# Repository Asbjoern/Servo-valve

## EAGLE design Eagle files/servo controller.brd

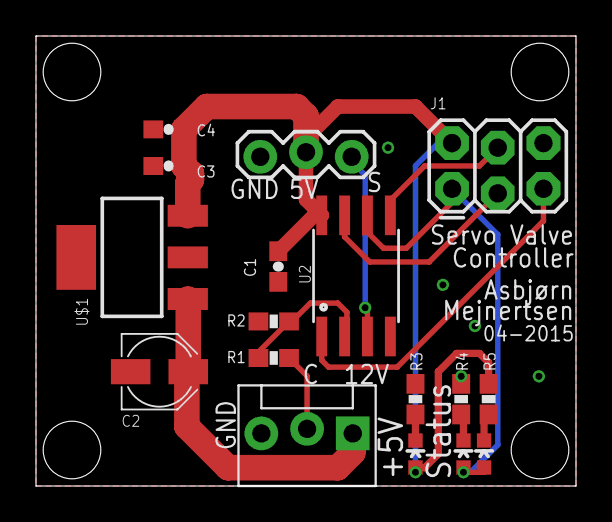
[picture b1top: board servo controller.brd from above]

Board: 4 copper layers, 30.0 x 25.0 mm, 17 parts (0 on the bottom side), 13 nets.

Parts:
C1: 100nF; 0603-CAP
C2: 10uF; PANASONIC_B
C3: 10uF; 0603-CAP
C4: 10nF; 0603-CAP
J1: AVR_SPI_PRG_62X3_LOCK; 2X3_LOCK
JP1: 1X03_LOCK
JP2: MOLEX-1X3_LOCK
LED1, LED2, LED3: LED-0603
R1: 11k; 0603-RES
R2: 7k5; 0603-RES
R3, R4, R5: 330; 0603-RES
U2: Tiny45-20-SMT; SO08-EIAJ
U$1: V_REG_MIC2920; SOT223

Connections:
5V: C1.2, C3.1, C4.1, J1.2, JP1.2, LED1.A, R5.1, U2.8, U$1.3
GND: C1.1, C2.-, C3.2, C4.2, J1.6, JP1.3, JP2.3, R2.1, R3.1, R4.1, U2.4, U$1.2
INPUT: R1.1, R2.2, U2.2
MISO: J1.1, LED2.A, U2.6
MOSI: J1.4, U2.5
unnamed: JP2.2, R1.2
unnamed: LED1.C, R3.2
unnamed: LED2.C, R4.2
unnamed: LED3.C, R5.2
RESET: J1.5, U2.1
SCK: J1.3, U2.7
SERVO: JP1.1, U2.3
VIN: C2.+, JP2.1, U$1.1

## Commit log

2015-05-08 Added sketchup and schematics
2015-05-22 Changed gear ratio to 27:36 to support 120deg servo

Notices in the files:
parts and their libraries:
SparkFun-Capacitors: Licensing: CC v3.0 Share-Alike You are welcome to use this library for commercial purposes.
